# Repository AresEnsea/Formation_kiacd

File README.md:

L'objectif est de former les étudiants à Kicad. 
Je recommande de passer 3 séances de 2H sur la création d'un shield pour qu'il découvre le logiciel.
Dans un deuxième temps, peut être les aider à réaliser un premier pcb complet, en profiter pour faire un multicouches

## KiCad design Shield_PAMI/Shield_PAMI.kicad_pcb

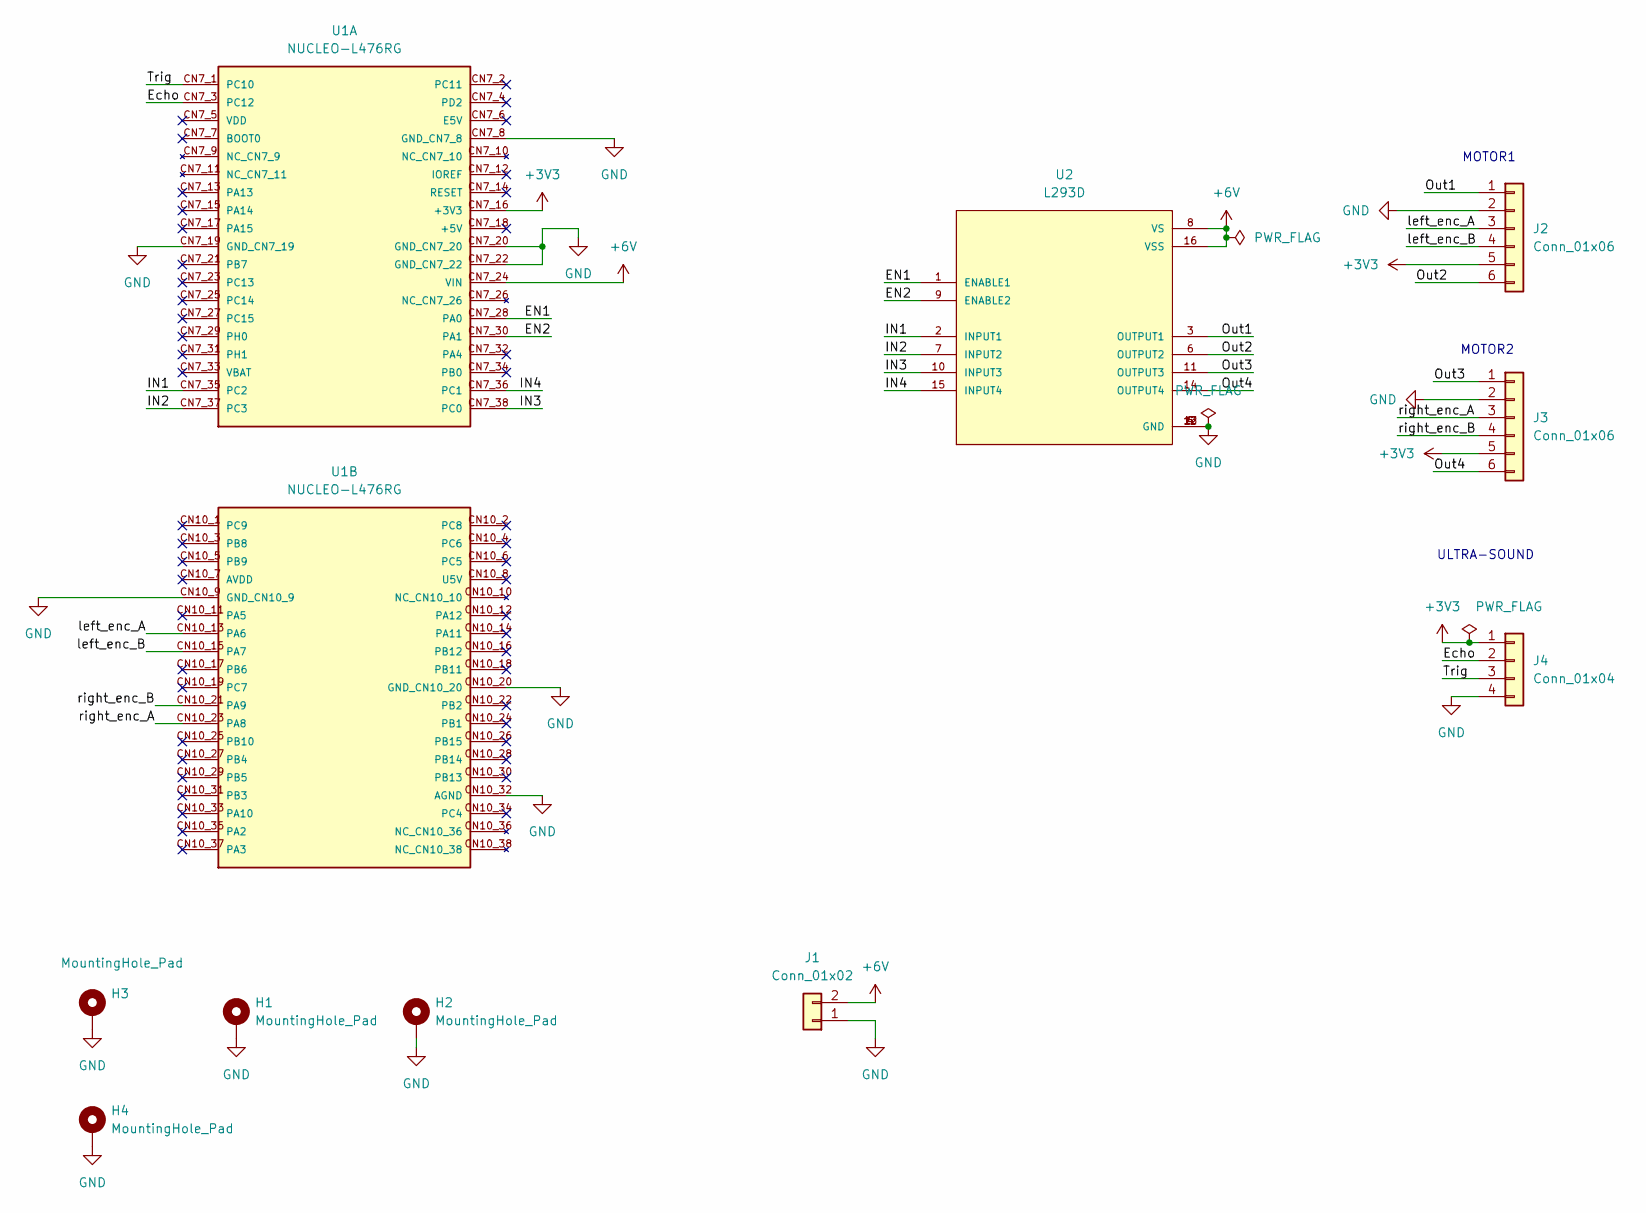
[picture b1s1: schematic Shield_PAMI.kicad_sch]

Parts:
H1, H2, H3, H4: MountingHole_Pad; MountingHole_2.2mm_M2_Pad_TopBottom
J1: Conn_01x02; JST_XH_B2B-XH-AM_1x02_P2.50mm_Vertical
J2, J3: Conn_01x06; JST_XH_B6B-XH-AM_1x06_P2.50mm_Vertical
J4: Conn_01x04; JST_XH_B4B-XH-AM_1x04_P2.50mm_Vertical
U1: NUCLEO-L476RG; MODULE_NUCLEO-L476RG; PARTREV 15; DigiKey_Part_Number 497-15881-ND
U2: L293D; DIP880W50P254L2000H510Q16; DigiKey_Part_Number 497-2936-5-ND

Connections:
+3V3: J2.5, J3.5, J4.1, U1.CN7_16 (+3V3)
+6V: J1.2, U1.CN7_24 (VIN), U2.8 (VS), U2.16 (VSS)
/EN1: U1.CN7_28 (PA0), U2.1 (ENABLE1)
/EN2: U1.CN7_30 (PA1), U2.9 (ENABLE2)
/Echo: J4.2, U1.CN7_3 (PC12)
/IN1: U1.CN7_35 (PC2), U2.2 (INPUT1)
/IN2: U1.CN7_37 (PC3), U2.7 (INPUT2)
/IN3: U1.CN7_38 (PC0), U2.10 (INPUT3)
/IN4: U1.CN7_36 (PC1), U2.15 (INPUT4)
/Out1: J2.1, U2.3 (OUTPUT1)
/Out2: J2.6, U2.6 (OUTPUT2)
/Out3: J3.1, U2.11 (OUTPUT3)
/Out4: J3.6, U2.14 (OUTPUT4)
/Trig: J4.3, U1.CN7_1 (PC10)
/left_enc_A: J2.3, U1.CN10_13 (PA6)
/left_enc_B: J2.4, U1.CN10_15 (PA7)
/right_enc_A: J3.3, U1.CN10_23 (PA8)
/right_enc_B: J3.4, U1.CN10_21 (PA9)
GND: H1.1 (1_1), H2.1 (1_1), H3.1 (1_1), H4.1 (1_1), J1.1, J2.2, J3.2, J4.4, U1.CN7_8 (GND_CN7_8), U1.CN7_19 (GND_CN7_19), U1.CN7_20 (GND_CN7_20), U1.CN7_22 (GND_CN7_22), U1.CN10_9 (GND_CN10_9), U1.CN10_20 (GND_CN10_20), U1.CN10_32 (AGND), U2.4 (GND), U2.5 (GND), U2.12 (GND), U2.13 (GND)

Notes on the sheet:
MOTOR2
MOTOR1
ULTRA-SOUND

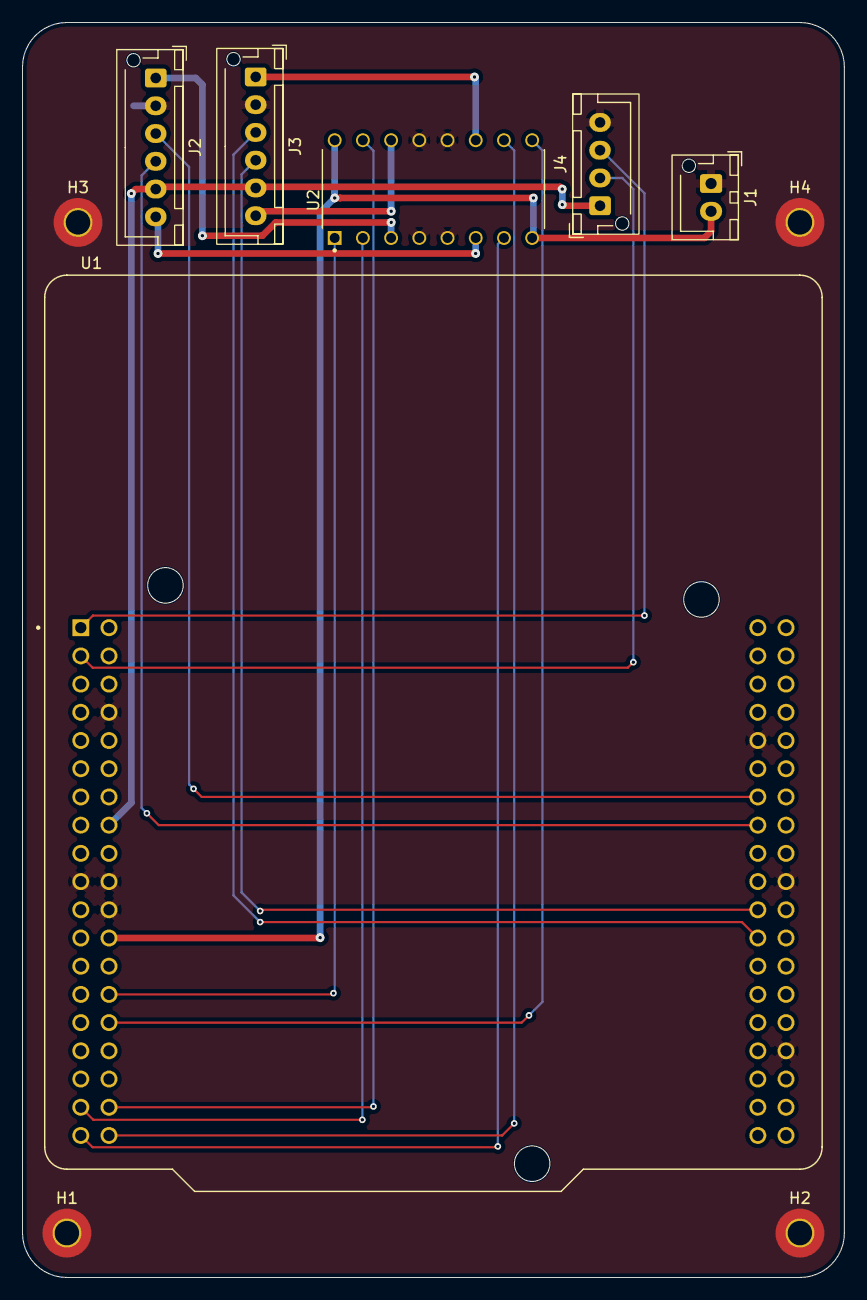
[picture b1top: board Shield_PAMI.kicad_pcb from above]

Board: 2 copper layers, 74.0 x 113.0 mm, 10 parts (0 on the bottom side), 19 nets.
